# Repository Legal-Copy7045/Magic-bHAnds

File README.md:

<p align="center">
  <picture>
    <source media="(prefers-color-scheme: dark)" srcset="docs/images/logo-dark.png">
    
  </picture>
</p>

<p align="center">

</p>

MagicbHAnds brings Disney MagicBands into **Home Assistant**. It has two
parts, which you can use separately or together, plus a Home Assistant
integration that ties them up.

| | What it does | Bands | Hardware |
|---|---|---|---|
| **Part 1: [MagicBand Bridge](docs/bridge.md)** | Lights up and buzzes bands from automations: any colour, animations, vibration patterns | MagicBand+ (Bluetooth) | An ESP32-S3 board, nothing else |
| **Part 2: [MagicBand Reader](docs/reader.md)** | A park-style tap point. Two white circles chase round the ring, Home Assistant knows whose band it is, a green glow (welcome) or two red pulses (denied) with sound, and a MagicBand+ lights up too | Original MagicBands and MagicBand+ (NFC) | ESP32-S3, PN532 NFC reader, LED ring (or strip), amplifier and speaker, powered by a USB-C charger. [Shopping list](hardware/shopping-list.md) |
| **[MagicbHAnds integration](docs/integration.md)** (HACS) | People and their bands (with or without a Home Assistant user), a log of every tap, the *Send MagicBand effect* action and the automation blueprints | Both | None |

## Quick start

**Building a reader?** Get the parts from the
[shopping list](hardware/shopping-list.md) and follow a step-by-step
build: the [breadboard](hardware/reader-breadboard/build.md) first, then the
[terminal base or point-to-point](hardware/reader-wired/build.md) or the
[compact (solderless)](hardware/reader-compact/build.md) version.
Each starts by flashing the bare ESP32 and checks every stage as you go. A
bridge needs no extra hardware.

1. **Flash the firmware** from the web installer:
   **https://legal-copy7045.github.io/Magic-bHAnds/**. Choose *Install the
   bridge* or *Install the reader*, then enter your Wi-Fi details. No YAML is
   needed. To change Wi-Fi later, the device starts a setup hotspot when it
   can't reach its Wi-Fi for 2 minutes (or use the web installer over USB).
2. **Add the device** in Home Assistant when it's discovered (ESPHome).
3. **Install the MagicbHAnds integration** from HACS:
   
   Restart Home Assistant, then add **MagicbHAnds** under Settings → Devices &
   services.
4. **Readers:** leave **Allow the device to perform Home Assistant actions**
   (the reader's ESPHome entry → Configure) **off**. Tag scans don't need it,
   and a reader outside your door shouldn't be able to call any action
   (see [docs/security.md](docs/security.md)).

Then:
- **Bridge:** call `magicband.send` from any automation, or use the
  *MagicBand+ notification* blueprint the integration installs.
- **Reader:** tap a band, then add it under **MagicbHAnds → Configure → Add or
  assign a band** and give it to a person.

## Features

**MagicBand Bridge** ([guide](docs/bridge.md))
- Palette colours, any RGB colour, two- and five-colour layouts, crossfades
  and 31 predefined park scenes, with one-press scene buttons
- Fast mode: mixes in the park's "fast mode" ping so bands respond sooner
- 11 vibration patterns, on-time, fade-out and stay-on control
- A MagicBand light entity with a colour picker and animation effects
- Several bridges for whole-house coverage, all addressed at once by default
- An optional Bluetooth proxy on the same board
- Also runs on other ESPHome boards, such as the SCREEK BP2-POE

**MagicBand Reader** ([guide](docs/reader.md), [ways to build it](hardware/README.md), [shopping list](hardware/shopping-list.md))
- Reads original MagicBands and MagicBand+ by their NFC ID
- An LED ring (or a flexible strip for tighter housings), with start-up,
  tap-in and error sounds
- Several ways to build it, each with a wiring diagram, a hole-by-hole wiring
  table and step-by-step instructions with checks:
  [breadboard](hardware/reader-breadboard/build.md),
  [terminal base and point-to-point](hardware/reader-wired/build.md),
  [compact (solderless)](hardware/reader-compact/build.md)
- Any LED count (1–100), RGB or SK6812 RGBW rings, and the whole tap
  sequence (colours, circles, welcome and denied timings, a dimmer idle glow
  at night, by set hours or sunset to sunrise) set from the reader's device
  page
- 28 light shows, played at start-up, from the device page, from
  `magicband.play_show` or on a schedule (blueprint), including holiday,
  birthday and passport-stamp shows
- Health sensors (Wi-Fi signal, memory, loop time, CPU temperature, restart
  reason) for spotting trouble
- Runs from one USB-C charger (20 W or more)
- Decides green or red on the device, instantly, even with Home Assistant
  offline
- Lights up and buzzes a MagicBand+ on a successful tap

**MagicbHAnds integration** ([guide](docs/integration.md))
- People with any number of bands, optionally linked to a Home Assistant
  person
- New bands are denied and announced; add them in a couple of clicks
- Allowed lists synced to every reader, with each reader's status shown and
  problems (a reader offline, a list it rejected) in Home Assistant's Repairs
- **Schedules and expiry** per band: a daily time window, days of the week,
  an end date
- **Enrolment**: tap a person's bands one after another to add them all
- **Personal welcome**: each person's bands welcomed in their own colour, on
  the ring and on their MagicBand+
- **Tap history** on the management page and in the logbook, and a battery
  sparkline for each MagicBand+
- **Charge reminders** for MagicBand+ (Repairs, an event, and a phone
  notification blueprint)
- A management page in the sidebar for bands, people, readers and bridges
  (administrators only), with health tiles for each reader and bridge
- `magicband_tap` events and per-person "last tap" sensors
- The `magicband.send` action and the bundled blueprints
- Logs which MagicBand+ devices Home Assistant's Bluetooth hears, and when,
  so you can see bands responding to a bridge
- Guest passes (start and end, number of uses, daily hours), lockdown (by
  hand, when nobody's home, at night or while the alarm is armed),
  birthday and holiday shows after a welcome, and a tap passport with
  streaks and stamps

## Releases and versions

The bridge firmware, the reader firmware and the integration share **one
version number** (see [`VERSION`](VERSION)). Each release is a
[GitHub Release](https://github.com/Legal-Copy7045/Magic-bHAnds/releases)
with notes from the [changelog](CHANGELOG.md), the firmware files and the
integration attached.

- **Firmware updates** appear in Home Assistant as an update on each bridge
  and reader, and install over Wi-Fi. Each device downloads its firmware itself
  from this project's site and only installs releases signed with the project's
  key. Turn on **Automatic updates** on a device to have it install new releases
  (only ever newer than the one it runs) by itself between 3 and 4 am in the device's **Time zone** (default
  Eastern). Devices keep time from an internet time server, so this works
  without Home Assistant.
- **Integration updates** appear in HACS.

To make a release: bump `VERSION` and the versions it lists (CI checks they
match), add a `CHANGELOG.md` section, and merge to `main`. The run for that
merge signs the firmware, tags `v<VERSION>` and publishes the GitHub Release
and the update site by itself. To retry a release that failed, go to **Actions → CI → Run
workflow**, tick **release**, and run it on `main`. Releases come
only from `main`: pushing a `v*` tag yourself doesn't release (it starts no
run, and the `release-signing` environment gives its key to `main` only).
To save GitHub Actions minutes, CI (`.github/workflows/ci.yml`, the owner's
project standard 1.1.0) runs on pull requests (not drafts: mark a pull request
ready once `python3 regression/run.py check` passes), once a week, and from Run
workflow; a pull request builds the firmware or runs the integration tests only
when it touches them. A merge to `main` only checks the private terms, and
releases when `VERSION` has no tag yet. Any push to `main` that raises `VERSION` signs the firmware and releases it,
so the GitHub account that can push to `main` is what protects releases: give
it two-factor authentication, and keep the `release-signing` environment
limited to `main` (see [docs/security.md](docs/security.md#accepted-risks)).

## Repo layout

| Path | What |
|---|---|
| `components/magicband/` | ESPHome component that broadcasts MagicBand+ commands |
| `esphome/magicband-bridge.yaml` | Bridge firmware (web installer, "Take control") |
| `esphome/magicband-reader.yaml` | Reader firmware (web installer, "Take control") |
| `esphome/magicband-addon.yaml` | The MagicBand parts as a package for any ESPHome board |
| `esphome/screek-bp2-poe*.yaml` | SCREEK BP2-POE as a PoE proxy and bridge |
| `esphome/sounds/` | The reader's sounds (the project owner's recordings) |
| `custom_components/magicband/` | The MagicbHAnds integration (HACS) |
| `homeassistant/` | Blueprints (notification, charge me), example scripts and automations, and the [management dashboard](homeassistant/dashboards/magicband.yaml) |
| `hardware/` | [Ways to build the reader](hardware/README.md), the [shopping list](hardware/shopping-list.md) (with generic alternatives), and the power diagram's generator |
| `hardware/reader-breadboard/` | Breadboard build: step-by-step build, spec and wiring table, and the diagram's generator |
| `hardware/reader-wired/` | Terminal base and point-to-point builds, with the interface board: step-by-step build and spec |
| `hardware/reader-compact/` | Compact (solderless) build: step-by-step build |
| `web/` | The web installer page |
| `docs/` | Guides: [bridge](docs/bridge.md), [reader](docs/reader.md), [integration](docs/integration.md), [commands](docs/commands.md), [protocol](docs/protocol.md), [SCREEK BP2-POE](docs/screek-bp2-poe.md), [security](docs/security.md); reader wiring diagrams; [ideas for later](docs/ideas.md) |
| `tests/` | Integration tests |

## Caveats

- Bands sleep to save battery. A sleeping band may need a shake or a longer
  burst before it reacts.
- The protocol is unofficial and reverse-engineered. See
  [docs/protocol.md](docs/protocol.md).
- This is for home tinkering. Don't run it anywhere near the parks.
- The reader builds have been reviewed against the parts' datasheets. The
  [compact build](hardware/reader-compact/build.md)
  has been built and tested on the USB-C PD supply (power, NFC, sound at
  100 %, a load test before the ring was fitted), and its 35-LED ring is
  wired and lights correctly (idle glow, all LEDs, colours, 5.1 V); the tap
  sequence and the load test with the ring are still to be confirmed. The breadboard, terminal-base and point-to-point
  builds have been reviewed but not built.
  Follow each build's staged tests, which check voltages before anything is
  connected to the ESP32.

## Security

A band's NFC ID and Bluetooth beacon identify it but don't prove it's
genuine, so a tap is about as secure as a basic RFID fob. Read
[docs/security.md](docs/security.md) before using MagicbHAnds to open a door.

## Credits

This project builds on other people's work.

**Protocol research**
- **[emcot.world: Disney MagicBand+ Bluetooth Codes](https://emcot.world/Disney_MagicBand%2B_Bluetooth_Codes)**:
  the community reverse-engineering wiki this project is based on. It covers
  the packet layouts, timing byte, vibration patterns, LED masks, colour
  palette, RGB command and the captured show animations. See
  [docs/protocol.md](docs/protocol.md).
- **[Haw8411/magic-band-plus-lights](https://github.com/Haw8411/magic-band-plus-lights)**
  (MIT): a Flipper Zero MagicBand+ app. Its preset list filled out the
  bridge's scenes, and its "Fast mode" (pre-warm and interleaved `CC 03 00 01 00`
  pings) is the basis for the bridge's Fast mode. The payloads are protocol
  data; no code was copied.
- **[xxfunprojectsxx/esp32_magicband](https://github.com/xxfunprojectsxx/esp32_magicband)**:
  an ESP32-S3 MagicBand+ broadcaster that we used to cross-check the command
  byte layouts and colour codes. No code was copied (that repo has no
  licence); this project's firmware was written independently.
- **[Adafruit: BLE Beacon NeoPixels](https://learn.adafruit.com/ble-beacon-neopixels)**:
  Adafruit's MagicBand+ beacon project, referenced by the emcot.world wiki.
  It was also one of the first sources found for this project.

**MagicBand reader projects** (inspiration for the reader; no code used)
- [Adafruit: Magic Band Reader](https://learn.adafruit.com/magic-band-reader):
  a Feather RP2040 reader. Its side-light NeoPixel strip is one of the
  flexible LED options for tight housings.
- [foolishmortalbuilders/magicbandreader](https://github.com/foolishmortalbuilders/magicbandreader):
  a Raspberry Pi reader with a pixel ring, Mickey and sounds.
- [dcivitano/Magic-Band-Reader](https://github.com/dcivitano/Magic-Band-Reader):
  an Arduino reader with an RC522, NeoPixels and a DFPlayer.
- [ncory/MagicReader](https://github.com/ncory/MagicReader): a Raspberry Pi
  reader with per-band sequences that triggers MagicBand+ effects through an
  ESP32 broadcaster.

**Sounds**
- The reader's start-up, tap-in and error sounds in `esphome/sounds/` were
  recorded by the project owner.

**Software and tools**
- [ESPHome](https://esphome.io): the firmware framework. The `magicband`
  component's raw-advertising approach follows ESPHome's `esp32_ble_beacon`
  component.
- [ESP Web Tools](https://esphome.github.io/esp-web-tools/) and
  [Improv Wi-Fi](https://www.improv-wifi.com): browser flashing and Wi-Fi
  setup on the install page.
- [Home Assistant](https://www.home-assistant.io): automations, the ESPHome
  integration and blueprints.
- [Espressif ESP-IDF](https://github.com/espressif/esp-idf): the ESP32
  Bluetooth stack.

**Font**
- **Waltograph** v4.2 by Justin Callaghan ([mickeyavenue.com](http://mickeyavenue.com/)),
  with Bill Shelly, Joshua Jones, Robert Johnson, John Hornbuckle, John Hansen,
  John Yaglenski and Erwin Denissen. It's used for the logo wordmark and the
  management page's headings. It's released under the
  [Creative Commons NonCommercial-ShareAlike licence](http://creativecommons.org/licenses/nc-sa/1.0/)
  for personal, noncommercial use. The font is in
  `custom_components/magicband/frontend/fonts/` with its own readme
  (`waltograph.txt`) and licence (`license.txt`), unchanged. The logo images made
  with it (`docs/images/logo*.png`, `custom_components/magicband/brand/*logo.png`)
  are shared under the same NonCommercial-ShareAlike licence.

**Hardware**
- Developed for the Lonely Binary ESP32-S3 N16R8 IPEX board, which uses the
  ESP32-S3-DevKitC-1 layout.
- The reader builds were checked against Espressif's DevKitC-1 guide,
  schematic and drawings; Elechouse's PN532 V3 manual and schematic; TI's
  74AHCT125, Worldsemi's WS2812B and Analog Devices' MAX98357A datasheets;
  and Adafruit's product pages and guides (NeoPixel Überguide, MAX98357A,
  HUSB238, PN532).

MagicBand and MagicBand+ are trademarks of Disney. The Waltograph font is a
fan-made lettering inspired by Disney's; it is not Disney's own typeface. This is an unofficial hobby
project with no affiliation to, or endorsement from, Disney, Adafruit or any of
the projects above.

## Development

```bash
pip install esphome
cd esphome
# Build against the local component instead of the copy on GitHub main:
esphome -s component_source ../components compile magicband-bridge.yaml
```

Hardware diagrams are generated, not drawn by hand:

```bash
python3 hardware/reader-breadboard/make_diagram.py > docs/reader-breadboard.svg
python3 hardware/reader-wired/make_diagrams.py terminal-base  > docs/reader-terminal-base.svg
python3 hardware/reader-wired/make_diagrams.py point-to-point > docs/reader-point-to-point.svg
python3 hardware/reader-wired/make_diagrams.py interface-board > docs/reader-interface-board.svg
python3 hardware/reader-wired/make_diagrams.py compact        > docs/reader-compact.svg
python3 hardware/make_power_diagram.py > docs/reader-power.svg
```

Releases: see [Releases and versions](#releases-and-versions). Once a
version is merged to `main`, devices offer the update in Home Assistant.

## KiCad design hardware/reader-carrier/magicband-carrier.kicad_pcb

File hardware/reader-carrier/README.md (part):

# MagicBand Reader carrier board (KiCad)

Build option 4 of [the ways to build the reader](../README.md).

A 90 × 64 mm, 2-layer "brains" board for the [MagicBand Reader](../../docs/reader.md),
with four M3 holes, sized for a 4.92 in (125 mm) box. It replaces the
breadboard, the power hubs, the interface board and the separate USB-C PD
trigger. The parts you already have plug in:

- the **ESP32-S3-DevKitC-1 (N16R8)** dev board, into two 22-pin sockets;
- the **MAX98357A amplifier kit**, by its own 5-wire cable (or an Adafruit
  3006 breakout straight into a 7-pin socket); the speaker plugs into the
  amplifier as before;
- the **LED ring** and the **PN532 NFC board**, on leads, so they can go
  wherever the housing needs them.

Every lead keeps the cable it uses on the breadboard: each plugs into a
2.54 mm female header wired in **that cable's own pin order**, so nothing is
re-crimped or crossed over.

[Schematic (PDF)](docs/schematic.pdf) · [Front](docs/front.svg) · [Back](docs/back.svg) · [DRC report](fab/drc.rpt)

> **Status: routed, design rules pass, not yet built.** Every net in the
> schematic matches the board pin for pin, the dev-board sockets follow
> Espressif's DevKitC-1 pinout, and the build checks every power track's
> width in the routed copper (below). Treat the first order as a prototype: get 5
> boards, power one up without the dev board first (below), and keep the
> compact build working until a board has been proven.

## What's on it

| | Part | Notes |
|---|---|---|
| J1 | USB-C (power only) | On the left edge |
| U1 | **CH224A** USB PD controller (or a CH224K) | Asks the charger for **5 V**, and nothing else: CFG1 is tied high through two 200 kΩ resistors side by side (R3, R9: either alone still holds it), so there's no switch to knock to 20 V. The CH224A is WCH's pin-compatible upgrade of the CH224K and the one JLCPCB stocks; wired per its datasheet (V2.1, 6.1.2) with **R1 and R2 = 0 Ω**. For a CH224K, fit **R1 = 1 kΩ and R2 = 10 kΩ** instead (6.2). D+/D− are left open (power only: the request goes over CC) |
| F1 | 3.5 A resettable fuse (1812, SMD1812P350TF/16) | Between USB-C and everything else. Sized for a warm box: see below |
| D2 | SMAJ5.0A TVS | Clamps spikes on the 5 V rail |
| D1 | Green LED, "5V OK" | Lights when the charger has agreed 5 V (the CH224A's PG) |
| D3 | SS34 Schottky | 5 V to the dev board. The board powers the ESP32, but the dev board's own USB can't power the LEDs and amplifier, so there's **no 5 V wire to pull** before using USB. (D3 stops the dev board's USB feeding the 5 V rail. What stops the charger feeding a computer through the dev board's USB port is the dev board's own diodes: check yours once, under First power-up) |
| U2 | 74AHCT1G125 | 3.3 V → 5 V LED data, then **470 Ω** (R7) |
| U3 | SRV05-4 | ESD clamp on the lines that leave the box: SDA, SCL, LED data |
| R5, R6 | 4.7 kΩ | I²C pull-ups to 3.3 V |
| R8 | 10 kΩ | Holds the LED data input low while the ESP32 boots (its pin floats until then), so the ring doesn't flash at power-up |
| C5 | 1000 µF 10 V | LED ring supply, by the ring connector |
| C6, C7 | 100 µF 16 V, 10 µF | Amplifier supply, by its header |
| TP1–TP3 | Test pads | 5 V, 3.3 V, GND |

GPIOs are the reader firmware's: I²S LRC 5, BCLK 6, DIN 7; I²C SDA 8, SCL 9;
LEDs 10. The firmware doesn't change: install the standard reader from the
[web installer](https://legal-copy7045.github.io/Magic-bHAnds/).

## Connectors and leads

| | Header (2.54 mm female) | Pins, left to right (1 = square pad) | Plug in | Lead length |
|---|---|---|---|---|
| J3 | 1×3 | **5V, DIN, GND** | The LED ring's 3-pin plug with its jumper wires: **red, green, black**. Use **22 AWG** for 5V and GND (the ring can draw 1.4 A), not thin jumper wire | Up to about 1 m |
| J2 | 1×4 | **GND, 5V, SDA, SCL** | The PN532's 4-wire Dupont cable, in the PN532's own order (GND, VCC, SDA, SCL). PN532 switches: 1 ON, 2 OFF (I²C) | Up to about 50 cm |
| J4 | 1×5 | **G, V, BCL, LRC, DIN** | The amplifier kit's cable, in the order printed by its socket. On the tested kit: **black G, red V, blue BCL, green LRC, yellow DIN**, black on the square pad | As supplied (about 20 cm) |
| J5 | 1×7 | LRC, BCLK, DIN, GAIN, SD, GND, Vin | An Adafruit 3006, *instead of* the kit on J4. Fit it parts-side up, so it stands out past the board's top edge (by about 10 mm) and not over the dev board | — |
| XJ1, XJ3 | 2 × 1×22, 22.86 mm apart | DevKitC-1 J1 and J3 | The dev board, **antenna end over the copper-free strip** (pin 1 on the right) | — |

The cables' male ends push into the headers the same way they push into a
breadboard. Once everything works, a dab of hot glue along each row keeps
them from working loose in the box. Labels on the board name every pin.

## Power tracks

### Current budget

Everything runs from the one USB-C input, so the worst case adds every
maximum at once (the same budget as the [shopping list](../shopping-list.md#current-budget-with-these-parts)):

| Load | Worst case |
|---|---|
| LED ring at full white | 1.44 A |
| Amplifier (MAX98357A into 4 Ω, full volume) | 0.65 A |
| Dev board (ESP32-S3, Wi-Fi transmit peak; *estimate*) | 0.50 A, through D3 |
| PN532 (*estimate*) | 0.15 A |
| Level shifter, pull-ups, LED | 0.01 A |
| **Total through USB-C, the fuse and the shared 5 V track** | **≈ 2.75 A**, under the charger's 3 A |

**The ring is capped by the firmware, not by its size.** 1.44 A is 24 RGB
LEDs × 60 mA. With more LEDs the reader scales its output down so full white
stays at about 1.44 A (24 ÷ LED count: a 35-LED ring runs at up to 68 %; an
RGBW ring is capped at 18 LEDs × 80 mA). That only works if the reader's
**LED count** setting matches the ring: set it before the first full-white
test. Without the cap, 35 LEDs × 60 mA would be 2.1 A for the ring and about
3.4 A in all, over a 3 A charger.

In normal use the reader draws about 0.3 A idle and about 1.4 A during a
welcome. The firmware's ring cap keeps the load inside the budget, and the
**charger's own 3 A limit is the short-circuit protection**: a 3.5 A fuse
can't trip on a 3 A supply. The fuse is a backstop for a supply that can
give more.

**Fuse and temperature.** A polyfuse's hold current falls as it gets warmer,
so it's sized for the inside of a closed box, not a 25 °C bench. From the
Ruilon SMD1812 datasheet (hold current, amps):

| | 25 °C | 40 °C | 50 °C | 60 °C | Trips at (25 °C) | Max voltage |
|---|---|---|---|---|---|---|
| SMD1812P300TF (3 A) | 3.00 | 2.55 | 2.28 | 2.01 | 5 A | 8 V |
| **SMD1812P350TF/16 (3.5 A, fitted)** | 3.50 | **2.98** | 2.66 | 2.35 | 6 A | 16 V |

The 3 A part would hold only 2.55 A at 40 °C, under the 2.75 A worst case.
The 3.5 A part holds it up to about 45 °C inside the box; the welcome load
(about 1.4 A) is far below either. Hold current is for an hour at that
current, so the full worst case, which lasts seconds, has more margin still.
It's the same 1812 size. The 16 V version is fitted because the plain
SMD1812P350TF is rated only 6 V, too close to a 5 V rail and the TVS's
clamp. If the box gets hotter than about 45 °C, or the ring is left on full
white for long, lower the ring's brightness rather than fit a bigger fuse.

### Track widths

| Net | Track | Carries (worst case) |
|---|---|---|
| VBUS (USB-C → fuse) | 0.8 mm | Everything, ≈ 2.75 A |
| +5V (fuse → ring, amplifier, NFC, and D3 to the dev board) | 1.2 mm | Up to ≈ 2.75 A by the fuse, less further along |
| ESP_5V (D3 → dev board) | 0.6 mm | ≤ 0.5 A |
| +3V3 | 0.4 mm | Pull-ups only |
| GND | 0.5 mm tracks plus solid pours on both sides | |

**Standard 1 oz copper.** By IPC-2221 (outer layer), 1.2 mm at 1 oz carries
about 2.7 A for a 10 °C rise and 0.8 mm about 2.0 A (2.8 A for 20 °C): the
full worst case (≈ 2.75 A, everything at maximum at once, which lasts seconds
and which the firmware's ring cap keeps rare) warms the 5 V track by about
10 °C, and the short 0.8 mm run from the socket to the fuse by about 20 °C.
At full load the board itself drops about 0.15–0.2 V between the socket and
the headers (mostly the fuse); the cable adds more. 2 oz copper would halve
the track's share, but at
2 oz JLCPCB needs 0.20 mm of solder mask between pads, exactly the gap
between the USB-C pins, and thicker copper makes the hand-soldered ground
pins harder to heat, so 1 oz is the better trade.

The only narrower pieces are necks into pads that are themselves narrower
than the track, no narrower than that pad, each under 3 mm: the two USB-C VBUS pins (0.6 mm, too
close together for more) and, depending on how the router lays it out, the
SRV05-4's 5 V pin or the 5V OK LED's resistor (a few mA). `tools/check_widths.py` measures the routed copper,
lists every neck, and fails the build on any other power track narrower than
this table. It also traces the copper from the fuse to every load (the ring,
amplifier and NFC headers, their capacitors and the dev board's diode) and
fails unless each is reached at full width, so a neck can only ever feed a
small part, never sit in the path to a load. It also checks vias: the 5 V path changes layer only at the
through-hole pins, and any via on VBUS or +5V must have a 0.8 mm drill, so a
via barrel is never the thinnest copper in the path.

### Ground and the speaker

On the breadboard, the sound crackled on the charger until the ESP32 had its
own ground wire to the amplifier: otherwise the I²S signals' ground return
ran through the power hub. The board does this in copper: ground pours fill
both sides (stitched together with vias), the dev board's four GND pins and
the amplifier header's G pin all join them directly, and the I²S tracks run
over that ground all the way. There's no jumper to add. If it ever crackles,
check the amplifier lead's G wire first.

## Compared with the tested build

The circuit is the [compact build](../reader-compact/build.md) that was
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
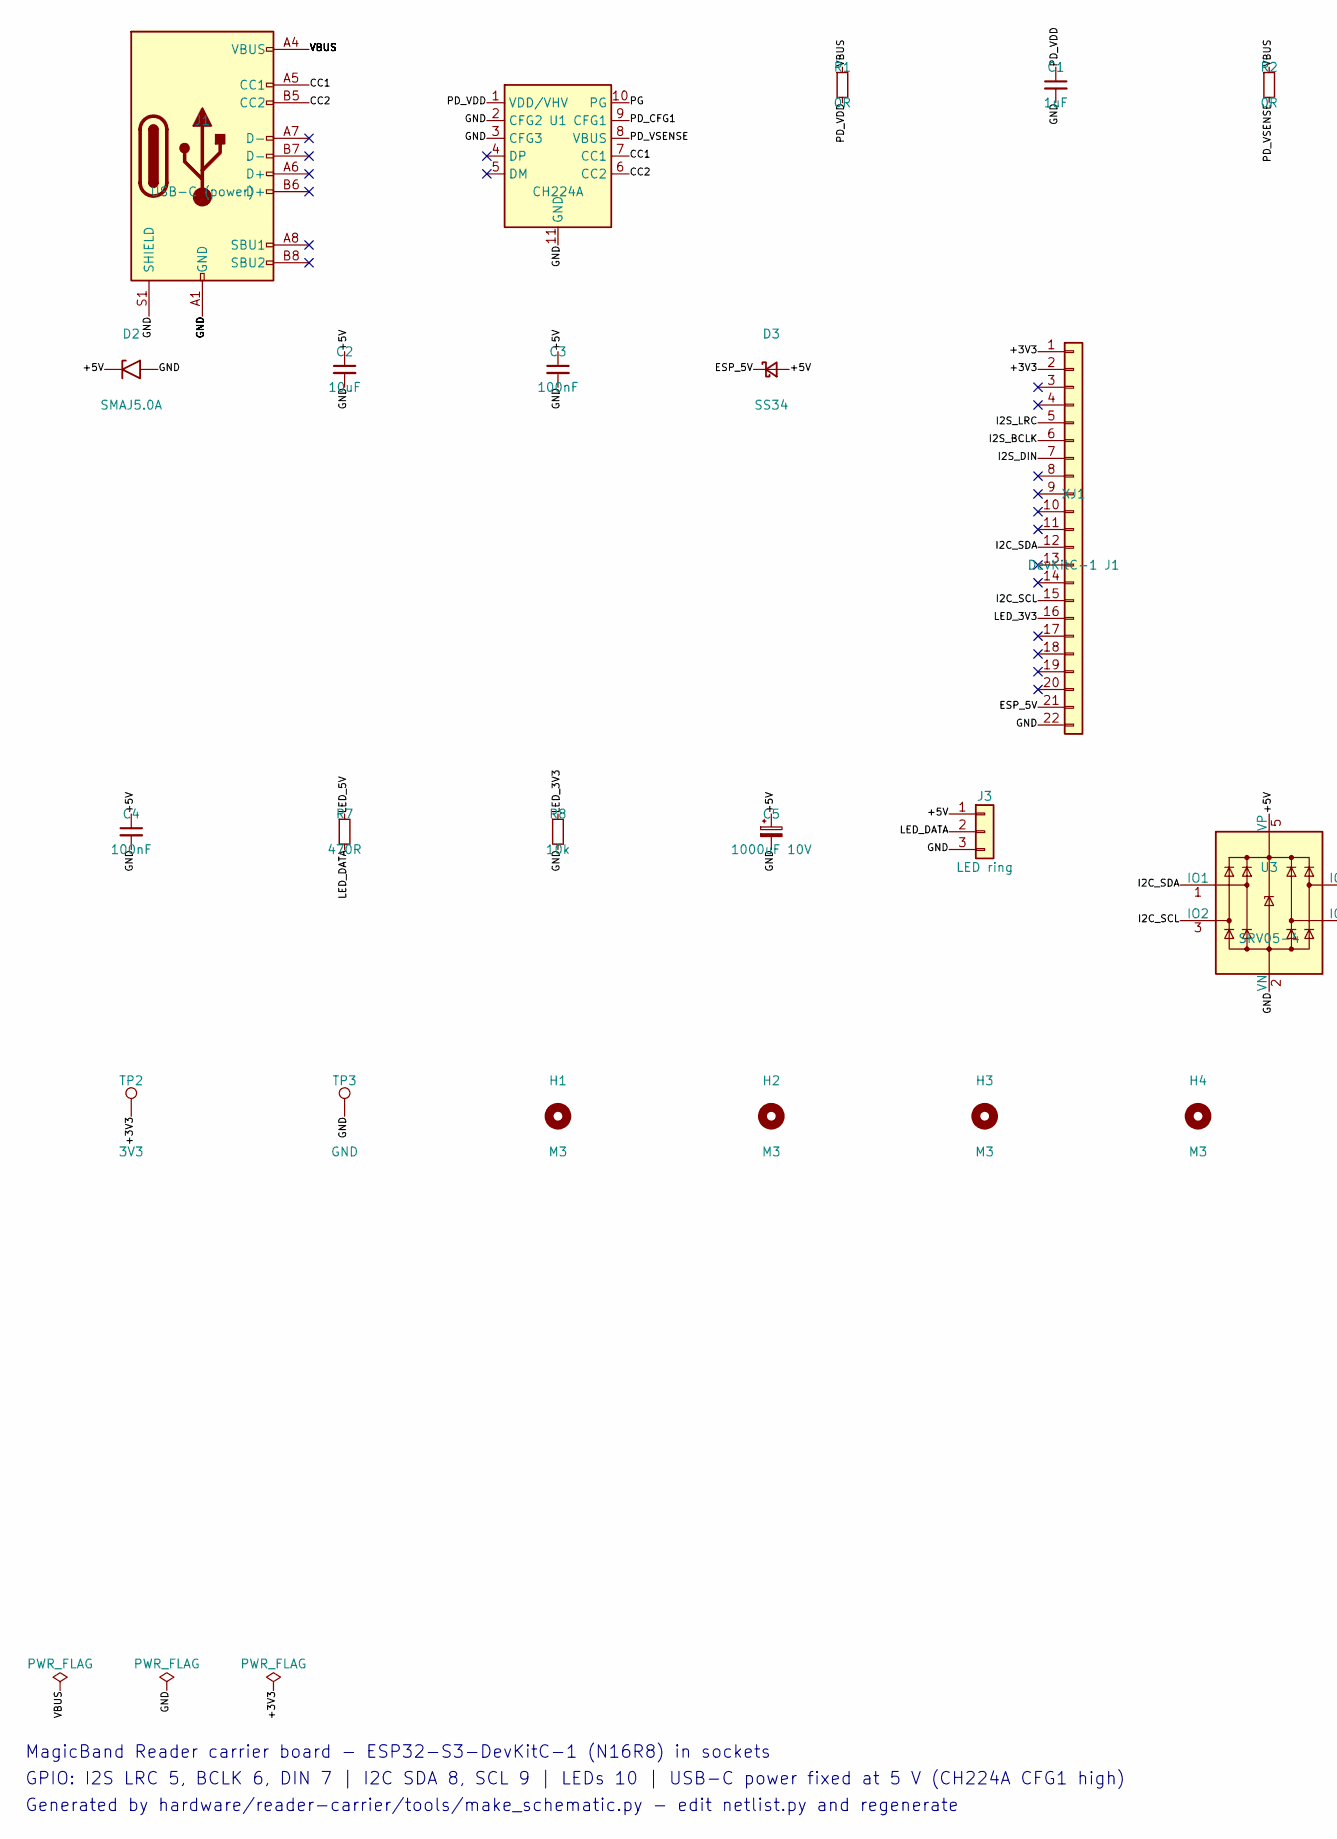
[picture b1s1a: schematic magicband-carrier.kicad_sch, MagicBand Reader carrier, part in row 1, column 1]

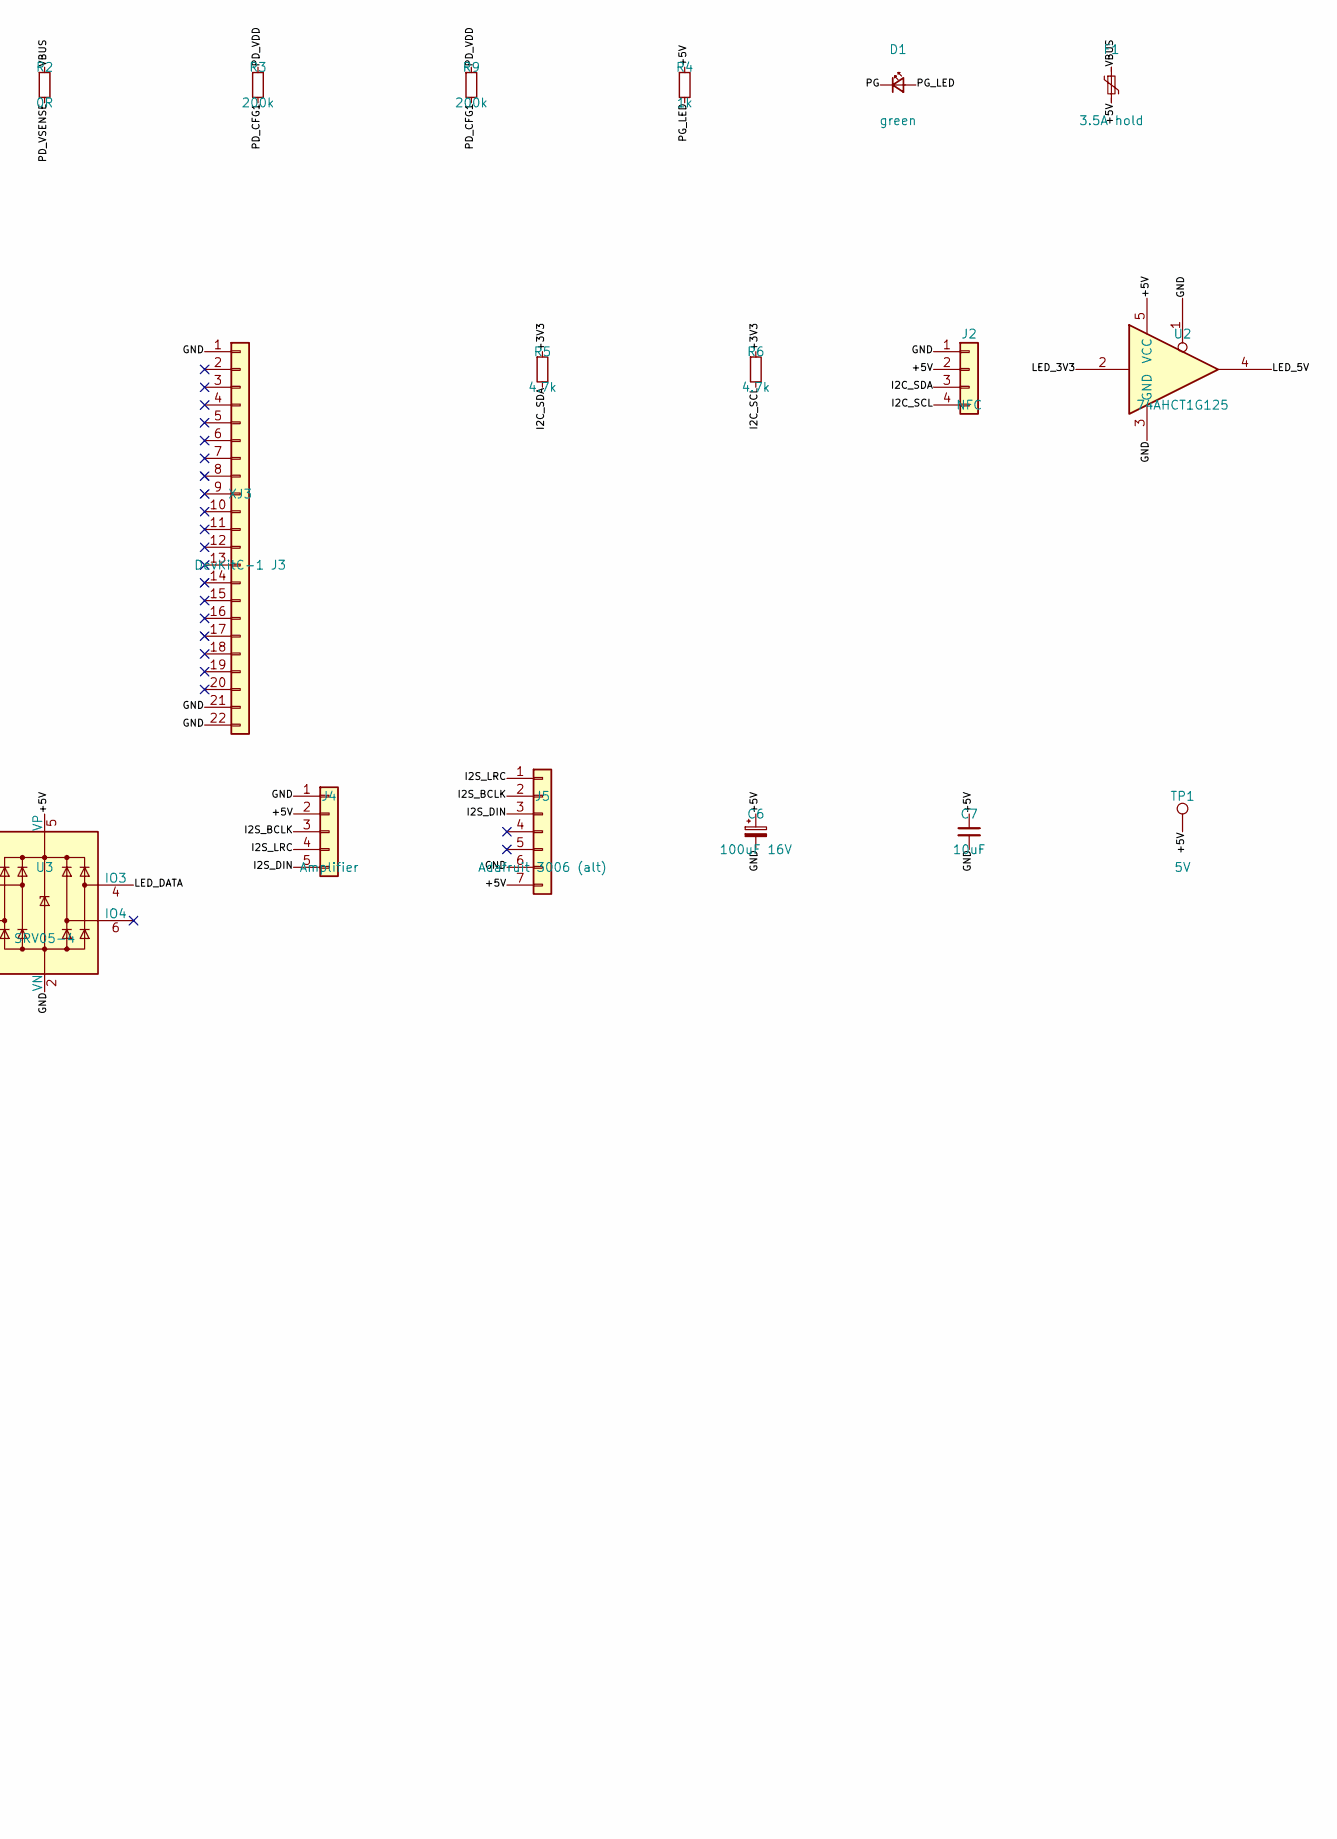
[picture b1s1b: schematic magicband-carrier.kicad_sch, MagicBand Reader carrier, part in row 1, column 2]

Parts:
C1: 1uF; C_0402_1005Metric; MPN CL05A105KA5NQNC; LCSC C52923
C2, C7: 10uF; C_0805_2012Metric; MPN CL21A106KAYNNNE; LCSC C15850
C3, C4: 100nF; C_0402_1005Metric; MPN CL05B104KO5NNNC; LCSC C1525
C5: 1000uF 10V; CP_Radial_D10.0mm_P5.00mm; MPN 1000 uF 10 V radial, 10 mm
C6: 100uF 16V; CP_Radial_D6.3mm_P2.50mm; MPN 100 uF 16 V radial, 6.3 mm
D1: green; LED_0603_1608Metric; MPN KT-0603G; LCSC C12624
D2: SMAJ5.0A; D_SMA; MPN SMAJ5.0A; LCSC C113952
D3: SS34; D_SMA; MPN SS34; LCSC C8678
F1: 3.5A hold; Fuse_1812_4532Metric; MPN SMD1812P350TF/16; LCSC C46970911
H1, H2, H3, H4: M3; MountingHole_3.2mm_M3
J1: USB-C (power); USB_C_Receptacle_HRO_TYPE-C-31-M-12_EdgeTrim; MPN TYPE-C-31-M-12; LCSC C165948
J2: NFC; PinSocket_1x04_P2.54mm_Vertical; MPN 2.54 mm 1x4 female header
J3: LED ring; PinSocket_1x03_P2.54mm_Vertical; MPN 2.54 mm 1x3 female header
J4: Amplifier; PinSocket_1x05_P2.54mm_Vertical; MPN 2.54 mm 1x5 female header
J5: Adafruit 3006 (alt); PinSocket_1x07_P2.54mm_Vertical; MPN 2.54 mm 1x7 female header
R1, R2: 0R; R_0402_1005Metric; MPN 0402WGF0000TCE; LCSC C17168
R3, R9: 200k; R_0402_1005Metric; MPN 0402WGF2003TCE; LCSC C25764
R4: 1k; R_0402_1005Metric; MPN 0402WGF1001TCE; LCSC C11702
R5, R6: 4.7k; R_0402_1005Metric; MPN 0402WGF4701TCE; LCSC C25900
R7: 470R; R_0402_1005Metric; MPN 0402WGF4700TCE; LCSC C25117
R8: 10k; R_0402_1005Metric; MPN 0402WGF1002TCE; LCSC C25744
TP1: 5V; TestPoint_Pad_D1.5mm
TP2: 3V3; TestPoint_Pad_D1.5mm
TP3: GND; TestPoint_Pad_D1.5mm
U1: CH224A; CH224K_ESSOP-10; MPN CH224A; LCSC C42459160
U2: 74AHCT1G125; SOT-23-5; MPN SN74AHCT1G125DBVR; LCSC C7484
U3: SRV05-4; SOT-23-6; MPN SRV05-4.TCT; LCSC C13612
XJ1: DevKitC-1 J1; PinSocket_1x22_P2.54mm_Vertical; MPN 2.54 mm 1x22 female header
XJ3: DevKitC-1 J3; PinSocket_1x22_P2.54mm_Vertical; MPN 2.54 mm 1x22 female header

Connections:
+3V3: R5.1, R6.1, TP2.1, XJ1.1, XJ1.2
+5V: C2.1, C3.1, C4.1, C5.1, C6.1, C7.1, D2.1 (A1), D3.2 (A), F1.2, J2.2, J3.1, J4.2, J5.7, R4.1, TP1.1, U2.5 (VCC), U3.5 (VP)
CC1: J1.A5 (CC1), U1.7 (CC1)
CC2: J1.B5 (CC2), U1.6 (CC2)
ESP_5V: D3.1 (K), XJ1.21
GND: C1.2, C2.2, C3.2, C4.2, C5.2, C6.2, C7.2, D2.2 (A2), J1.A1 (GND), J1.A12 (GND), J1.B1 (GND), J1.B12 (GND), J1.S1 (SHIELD), J2.1, J3.3, J4.1, J5.6, R8.2, TP3.1, U1.2 (CFG2), U1.3 (CFG3), U1.11 (GND), U2.1, U2.3 (GND), U3.2 (VN), XJ1.22, XJ3.1, XJ3.21, XJ3.22
I2C_SCL: J2.4, R6.2, U3.3 (IO2), XJ1.15
I2C_SDA: J2.3, R5.2, U3.1 (IO1), XJ1.12
I2S_BCLK: J4.3, J5.2, XJ1.6
I2S_DIN: J4.5, J5.3, XJ1.7
I2S_LRC: J4.4, J5.1, XJ1.5
LED_3V3: R8.1, U2.2, XJ1.16
LED_5V: R7.1, U2.4
LED_DATA: J3.2, R7.2, U3.4 (IO3)
PD_CFG1: R3.2, R9.2, U1.9 (CFG1)
PD_VDD: C1.1, R1.2, R3.1, R9.1, U1.1 (VDD/VHV)
PD_VSENSE: R2.2, U1.8 (VBUS)
PG: D1.1 (K), U1.10 (PG)
PG_LED: D1.2 (A), R4.2
VBUS: F1.1, J1.A4 (VBUS), J1.A9 (VBUS), J1.B4 (VBUS), J1.B9 (VBUS), R1.1, R2.1

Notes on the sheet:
MagicBand Reader carrier board - ESP32-S3-DevKitC-1 (N16R8) in sockets
GPIO: I2S LRC 5, BCLK 6, DIN 7 | I2C SDA 8, SCL 9 | LEDs 10 | USB-C power fixed at 5 V (CH224A CFG1 high)
Generated by hardware/reader-carrier/tools/make_schematic.py - edit netlist.py and regenerate

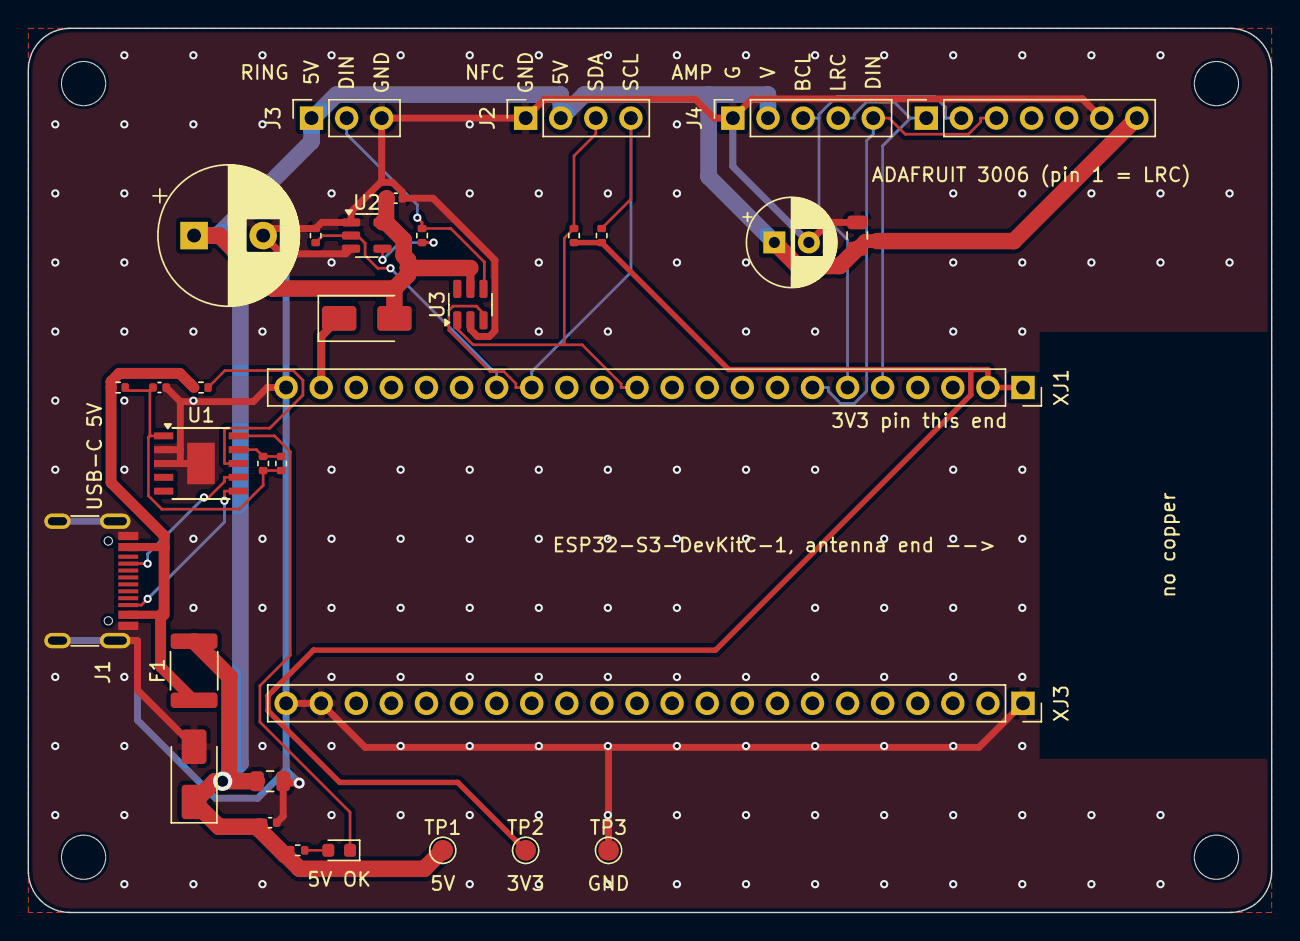
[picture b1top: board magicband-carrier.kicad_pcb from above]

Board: 2 copper layers, 90.0 x 64.0 mm, 37 parts (0 on the bottom side), 20 nets.

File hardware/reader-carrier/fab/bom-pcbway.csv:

Item #,Designator,Qty,Manufacturer,Mfg Part #,Description / Value,Package / Footprint,Type,LCSC Part #,Notes
1,C1,1,Samsung Electro-Mechanics,CL05A105KA5NQNC,1uF,0402,SMD,C52923,
2,"C2,C7",2,Samsung Electro-Mechanics,CL21A106KAYNNNE,10uF,0805,SMD,C15850,
3,"C3,C4",2,Samsung Electro-Mechanics,CL05B104KO5NNNC,100nF,0402,SMD,C1525,
4,D1,1,Hubei KENTO Elec,KT-0603G,green,0603,SMD,C12624,Polarised: cathode to pad 1
5,D2,1,MDD (Microdiode Semiconductor),SMAJ5.0A,SMAJ5.0A,SMA (DO-214AC),SMD,C113952,Unidirectional TVS: cathode (band) to pad 1
6,D3,1,MDD (Microdiode Semiconductor),SS34,SS34,SMA (DO-214AC),SMD,C8678,Polarised: cathode (band) to pad 1
7,F1,1,RUILON (Shenzhen Ruilongyuan Elec),SMD1812P350TF/16,3.5A hold,1812,SMD,C46970911,No substitute: must be the 16 V version (/16)
8,J1,1,Korean Hroparts Elec (HRO),TYPE-C-31-M-12,USB-C (power),USB-C 16-pin SMD + 4 through-hole shell tabs,SMD,C165948,No substitute. Overhangs the board edge 0.5 mm by design; solder the 4 shell tabs
9,"R1,R2",2,UNI-ROYAL (Uniroyal Elec),0402WGF0000TCE,0R,0402,SMD,C17168,
10,"R3,R9",2,UNI-ROYAL (Uniroyal Elec),0402WGF2003TCE,200k,0402,SMD,C25764,
11,R4,1,UNI-ROYAL (Uniroyal Elec),0402WGF1001TCE,1k,0402,SMD,C11702,
12,"R5,R6",2,UNI-ROYAL (Uniroyal Elec),0402WGF4701TCE,4.7k,0402,SMD,C25900,
13,R7,1,UNI-ROYAL (Uniroyal Elec),0402WGF4700TCE,470R,0402,SMD,C25117,
14,R8,1,UNI-ROYAL (Uniroyal Elec),0402WGF1002TCE,10k,0402,SMD,C25744,
15,U1,1,WCH (Jiangsu Qin Heng),CH224A,CH224A,ESSOP-10 (exposed pad),SMD,C42459160,"No substitute. Pin 1 at the silkscreen triangle. Exposed pad is GND, must be soldered"
16,U2,1,Texas Instruments,SN74AHCT1G125DBVR,74AHCT1G125,SOT-23-5,SMD,C7484,Pin 1 at the silkscreen triangle
17,U3,1,Semtech,SRV05-4.TCT,SRV05-4,SOT-23-6,SMD,C13612,Pin 1 at the silkscreen triangle

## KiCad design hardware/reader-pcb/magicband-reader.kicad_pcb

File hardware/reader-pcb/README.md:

# MagicBand Reader PCB (KiCad)

Build option 4 of [the ways to build the reader](../README.md).

A 26 × 58 mm, 2-layer board for the [MagicBand Reader](../../docs/reader.md).
It replaces the dev board, amplifier module, level shifter and breadboard.
The NFC reader, speaker and LEDs plug in on leads.

[Schematic (PDF)](docs/schematic.pdf) · [Front](docs/front.svg) · [Back](docs/back.svg) · [DRC report](fab/drc.rpt)

> **Status: routed, design rules pass, ready to order, but not yet built or
> tested.** Treat the first order as a prototype: get 5 boards, check them
> before connecting the LEDs, and keep the dev-board version working until
> one has been proven.

## What's on it

| | Part | Notes |
|---|---|---|
| U1 | ESP32-S3-WROOM-1-**N16R8** | Same chip, flash and PSRAM as the dev board. Antenna along the top edge, with no copper under it |
| J1 | USB-C (GCT USB4105) | Power and flashing (native USB), 5.1 kΩ CC resistors, USBLC6 ESD protection |
| U2 | AMS1117-3.3 | 3.3 V for the ESP32 and the NFC reader |
| U3 | MAX98357A | I2S amplifier, mono, 9 dB gain |
| U4 | 74AHCT1G125 | 3.3 V → 5 V LED data, with a 330 Ω series resistor |
| SW1, SW2 | RESET, BOOT | |

GPIOs match the reader firmware: I2S LRCLK 5, BCLK 6, DOUT 7; I2C SDA 8,
SCL 9; LEDs 10.

## Connectors (leads)

| | Connector | Pins | Goes to |
|---|---|---|---|
| J2 | JST **SH** 1.0 mm, 4-pin, left edge | GND, 3V3, SDA, SCL | PN532 (I2C mode). Qwiic / STEMMA QT order, so a Qwiic-to-Dupont lead fits a PN532 module's header |
| J3 | JST **PH** 2.0 mm, 2-pin, left edge | SPK+, SPK− | 4–8 Ω speaker, 3 W max |
| J4 | JST **PH** 2.0 mm, 3-pin, right edge | 5V, DATA, GND | LED ring DIN; chain the Mickey head off the ring's DOUT |

All connectors are side-entry, so leads leave flat along the board.

## Power

Everything runs from the USB-C port, LEDs included. Use a USB-C charger
that offers **5 V 3 A** (most do). 36 LEDs at full white draw ~2 A, and the
reader's default brightness is well below that. A plain USB-A port gives
0.5–1.5 A, which is fine for the board but not for bright LEDs.

## Firmware

Use **Reader on the custom PCB** in the web installer, built from
[`esphome/magicband-reader-pcb.yaml`](../../esphome/magicband-reader-pcb.yaml).
It's the standard reader with logs and Wi-Fi setup on the ESP32-S3's native
USB port (the board has no USB-serial chip), and it updates on its own
channel. Plug in USB-C, click install; if the board isn't detected, hold
**BOOT**, tap **RESET**, release **BOOT**, and try again.

Once it's running, go through the checks in
[hardware/README.md](../README.md#checking-a-build-works).

## How it's made

Everything is generated by scripts in `tools/` from one parts list
(`tools/netlist.py`), so the schematic and board can't disagree. The
schematic's netlist was exported from KiCad and checked against it.

- `make_schematic.py`: the schematic, with every pin labelled by net name.
- `make_pcb.py`: footprints, placement, outline, ground pours.
- `export_dsn.py` → **Freerouting 1.9.0** → `import_ses.py`: autorouting.
  Ground is routed as tracks too, then the ground pours go back on and
  stitching vias tie the two sides together.
- `make_fab.py`: the JLCPCB BOM and placement file.
- `build.sh` runs it all, including the design-rule check and Gerber export.

The design-rule check (`fab/drc.rpt`) has **no errors and no unconnected
pads**. The remaining entries are notices that the stock KiCad libraries
aren't configured on the build machine, and silkscreen warnings where the
module outline meets the board edge (the fab trims these).

Net classes: +5V and +3V3 0.4 mm, GND and speaker 0.3 mm, USB 0.25 mm,
signals 0.2 mm. The strip under the antenna has no copper on either side.

To change the design, edit `netlist.py` or `make_pcb.py` and run
`tools/build.sh`, or open `magicband-reader.kicad_pro` in KiCad and edit it
directly (then stop using the scripts, which would overwrite your changes).

## Ordering (JLCPCB)

1. Upload **`fab/magicband-reader-gerbers.zip`** (Gerbers and drill file)
   at jlcpcb.com. 2 layers, 1.6 mm, any colour. Turn on **PCB Assembly**,
   top side.
3. Upload `fab/bom.csv` and `fab/cpl.csv`. Parts with an LCSC number match
   automatically. Search for the others by MPN (USB4105-GF-A, the JST SH/PH
   connectors, B3U-1000P, SN74AHCT1G125DBVR) or pick equivalents. **Check
   every match and rotation in JLC's preview**, especially U1, U3 and J1.

4. Tick "Confirm parts placement" so JLC's engineers check rotations too.

Design rules: 0.2 mm minimum tracks, 0.15 mm minimum clearance (0.2 mm
between different nets in practice), 0.6/0.3 mm vias, 0.3 mm smallest
drill. All within JLCPCB's standard 2-layer process. The USB-C socket's
plastic pegs sit 0.19 mm from a pad in GCT's own footprint, which is normal
for that part.

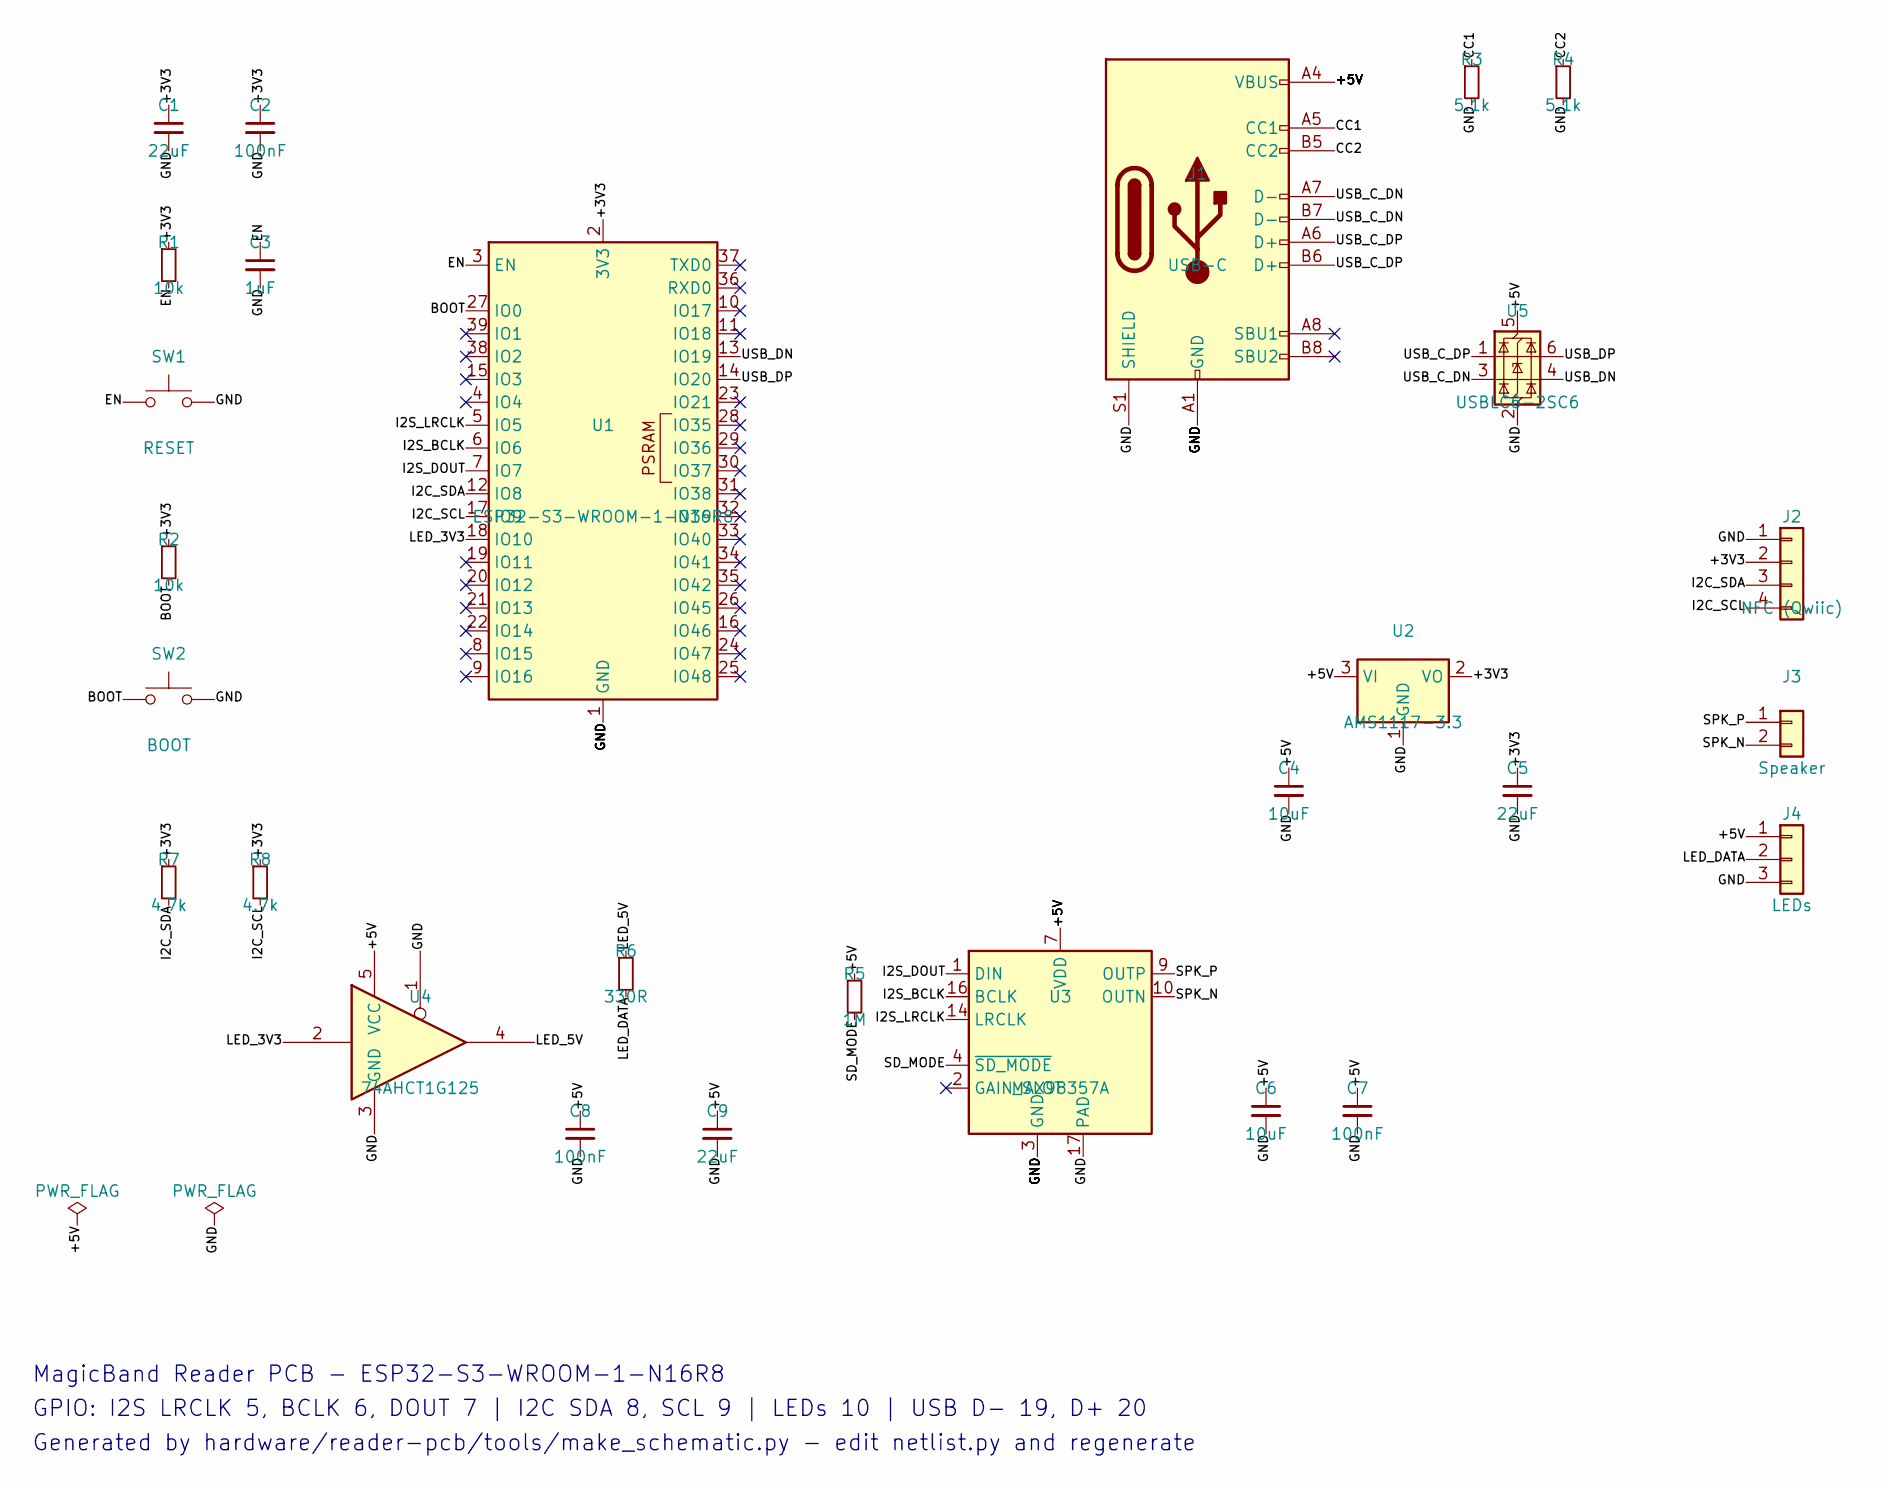
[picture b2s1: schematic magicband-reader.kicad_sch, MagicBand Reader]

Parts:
C1, C5, C9: 22uF; C_0805_2012Metric; MPN CL21A226MAQNNNE; LCSC C45783
C2, C7, C8: 100nF; C_0402_1005Metric; MPN CL05B104KO5NNNC; LCSC C1525
C3: 1uF; C_0402_1005Metric; MPN CL05A105KA5NQNC; LCSC C52923
C4, C6: 10uF; C_0805_2012Metric; MPN CL21A106KAYNNNE; LCSC C15850
J1: USB-C; USB_C_Receptacle_GCT_USB4105-xx-A_16P_TopMnt_Horizontal; MPN USB4105-GF-A
J2: NFC (Qwiic); JST_SH_SM04B-SRSS-TB_1x04-1MP_P1.00mm_Horizontal; MPN SM04B-SRSS-TB(LF)(SN)
J3: Speaker; JST_PH_S2B-PH-SM4-TB_1x02-1MP_P2.00mm_Horizontal; MPN S2B-PH-SM4-TB(LF)(SN)
J4: LEDs; JST_PH_S3B-PH-SM4-TB_1x03-1MP_P2.00mm_Horizontal; MPN S3B-PH-SM4-TB(LF)(SN)
R1, R2: 10k; R_0402_1005Metric; MPN 0402WGF1002TCE; LCSC C25744
R3, R4: 5.1k; R_0402_1005Metric; MPN 0402WGF5101TCE; LCSC C25905
R5: 1M; R_0402_1005Metric; MPN 0402WGF1004TCE; LCSC C26083
R6: 330R; R_0402_1005Metric; MPN 0402WGF3300TCE; LCSC C25104
R7, R8: 4.7k; R_0402_1005Metric; MPN 0402WGF4701TCE; LCSC C25900
SW1: RESET; SW_SPST_B3U-1000P; MPN B3U-1000P
SW2: BOOT; SW_SPST_B3U-1000P; MPN B3U-1000P
U1: ESP32-S3-WROOM-1-N16R8; ESP32-S3-WROOM-1; MPN ESP32-S3-WROOM-1-N16R8; LCSC C2913202
U2: AMS1117-3.3; SOT-223-3_TabPin2; MPN AMS1117-3.3; LCSC C6186
U3: MAX98357A; TQFN-16-1EP_3x3mm_P0.5mm_EP1.23x1.23mm; MPN MAX98357AETE+T; LCSC C910544
U4: 74AHCT1G125; SOT-23-5; MPN SN74AHCT1G125DBVR
U5: USBLC6-2SC6; SOT-23-6; MPN USBLC6-2SC6; LCSC C7519

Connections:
+3V3: C1.1, C2.1, C5.1, J2.2, R1.1, R2.1, R7.1, R8.1, U1.2 (3V3), U2.2 (VO)
+5V: C4.1, C6.1, C7.1, C8.1, C9.1, J1.A4 (VBUS), J1.A9 (VBUS), J1.B4 (VBUS), J1.B9 (VBUS), J4.1, R5.1, U2.3 (VI), U3.7 (VDD), U3.8 (VDD), U4.5 (VCC), U5.5 (VBUS)
BOOT: R2.2, SW2.1, U1.27 (IO0)
CC1: J1.A5 (CC1), R3.1
CC2: J1.B5 (CC2), R4.1
EN: C3.1, R1.2, SW1.1, U1.3 (EN)
GND: C1.2, C2.2, C3.2, C4.2, C5.2, C6.2, C7.2, C8.2, C9.2, J1.A1 (GND), J1.A12 (GND), J1.B1 (GND), J1.B12 (GND), J1.S1 (SHIELD), J2.1, J2.MP, J3.MP, J4.3, J4.MP, R3.2, R4.2, SW1.2, SW2.2, U1.1 (GND), U1.40 (GND), U1.41 (GND), U2.1 (GND), U3.3 (GND), U3.11 (GND), U3.15 (GND), U3.17 (PAD), U4.1, U4.3 (GND), U5.2 (GND)
I2C_SCL: J2.4, R8.2, U1.17 (IO9)
I2C_SDA: J2.3, R7.2, U1.12 (IO8)
I2S_BCLK: U1.6 (IO6), U3.16 (BCLK)
I2S_DOUT: U1.7 (IO7), U3.1 (DIN)
I2S_LRCLK: U1.5 (IO5), U3.14 (LRCLK)
LED_3V3: U1.18 (IO10), U4.2
LED_5V: R6.1, U4.4
LED_DATA: J4.2, R6.2
SD_MODE: R5.2, U3.4 (~SD_MODE)
SPK_N: J3.2, U3.10 (OUTN)
SPK_P: J3.1, U3.9 (OUTP)
USB_C_DN: J1.A7 (D-), J1.B7 (D-), U5.3 (I/O2)
USB_C_DP: J1.A6 (D+), J1.B6 (D+), U5.1 (I/O1)
USB_DN: U1.13 (IO19), U5.4 (I/O2)
USB_DP: U1.14 (IO20), U5.6 (I/O1)

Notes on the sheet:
MagicBand Reader PCB - ESP32-S3-WROOM-1-N16R8
GPIO: I2S LRCLK 5, BCLK 6, DOUT 7 | I2C SDA 8, SCL 9 | LEDs 10 | USB D- 19, D+ 20
Generated by hardware/reader-pcb/tools/make_schematic.py - edit netlist.py and regenerate
